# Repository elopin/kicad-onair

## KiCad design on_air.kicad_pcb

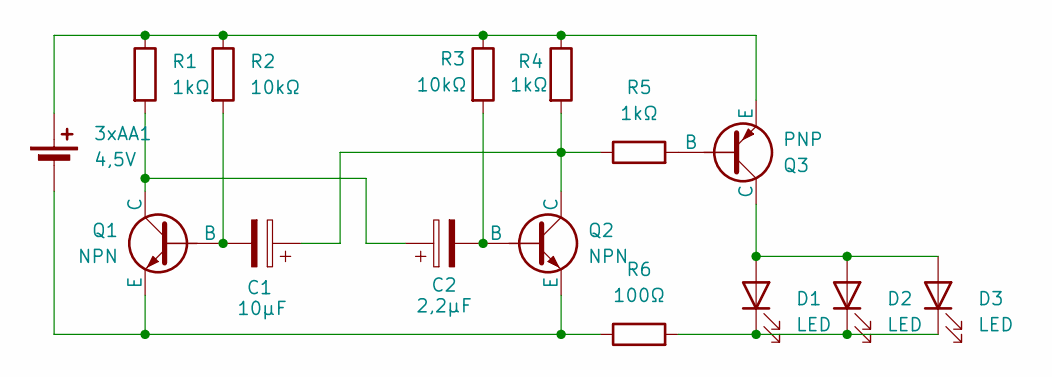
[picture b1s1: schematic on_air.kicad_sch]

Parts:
3xAA1: 4,5V; PinHeader_1x02_P1.00mm_Horizontal
C1: 10μF; CP_Radial_D5.0mm_P2.50mm
C2: 2,2µF; CP_Radial_D5.0mm_P2.50mm
D1, D2, D3: LED; LED_D5.0mm_Clear
Q1, Q2: NPN; TO-92
Q3: PNP; TO-92
R1, R4, R5: 1kΩ; R_Axial_DIN0207_L6.3mm_D2.5mm_P7.62mm_Horizontal
R2, R3: 10kΩ; R_Axial_DIN0207_L6.3mm_D2.5mm_P7.62mm_Horizontal
R6: 100Ω; R_Axial_DIN0207_L6.3mm_D2.5mm_P7.62mm_Horizontal

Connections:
unnamed: 3xAA1.1 (+), Q3.3 (E), R1.1, R2.1, R3.1, R4.1
unnamed: 3xAA1.2 (-), Q1.3 (E), Q2.3 (E), R6.1
unnamed: D1.2 (A), D2.2 (A), D3.2 (A), Q3.1 (C)
unnamed: D1.1 (K), D2.1 (K), D3.1 (K), R6.2
unnamed: C1.2, Q1.2 (B), R2.2
unnamed: C2.1, Q1.1 (C), R1.2
unnamed: C2.2, Q2.2 (B), R3.2
unnamed: C1.1, Q2.1 (C), R4.2, R5.1
unnamed: Q3.2 (B), R5.2

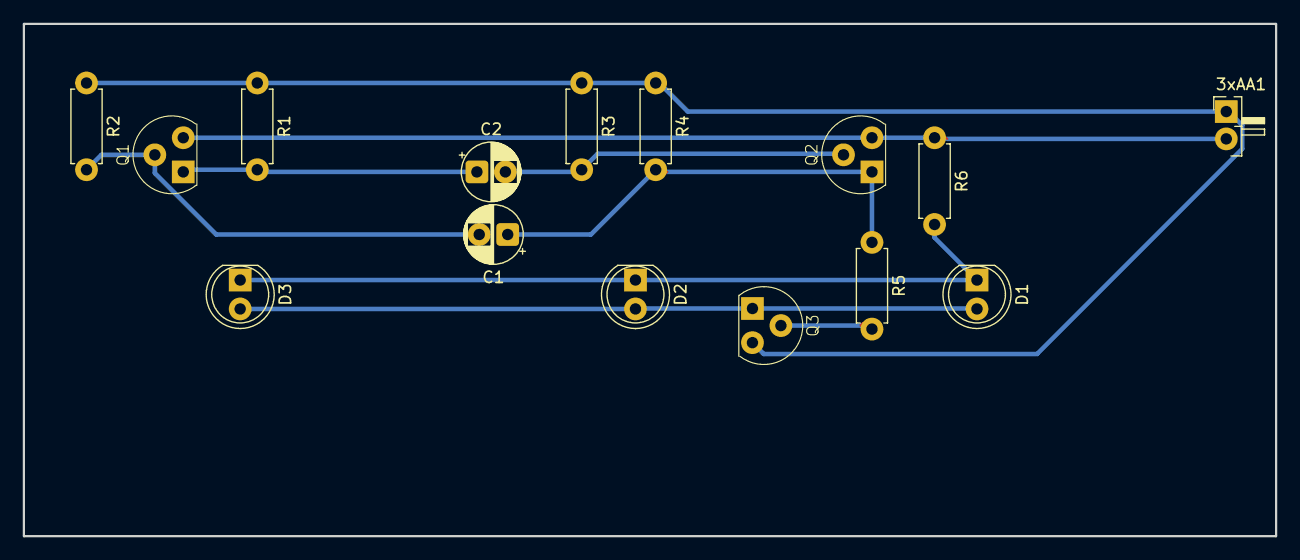
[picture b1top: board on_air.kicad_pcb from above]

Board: 2 copper layers, 110.0 x 45.0 mm, 15 parts (0 on the bottom side), 9 nets.

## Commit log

2025-12-29 init repo
2025-12-29 test notebook
2026-01-30 B.Cu
